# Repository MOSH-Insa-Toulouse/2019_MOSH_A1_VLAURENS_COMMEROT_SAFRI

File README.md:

<header>

 </header>
 <h1 style="text-align:center" >2019_MOSH_A1_VLAURENS_COMMEROT_SAFRI</h1>
<a href="./README_EN.md">Version Anglaise du README</a>

 ## Contenu

Ce projet KiCad contient le code source des TP sur Arduino et les fichiers de conception du shield réalisé dans le cadre du projet sur le capteur de Gaz", à savoir :
    La partie schématique, décrivant le circuit électronique implémenté (composants, routage des pins)
    La partie en couche, décrivant la forme de la carte, l’emplacement des différents éléments sur celle-ci et la trajectoire des pistes de routage.
    Une vu 3D montrant les résultat visuel de la carte lors qu'elle sera designé.

## 1. Travaux Pratiques sur Arduino

Ces travaux pratiques avaient pour principal objectif de nous apprendre à développer la partie intelligente de nos capteurs de gaz. En d'autres mots nous avons dans cette partie appris la composition d'une carte Arduino. Nous avons appris à pousser et tester des programmes sur le micro-controleur ATMEGA128 qui le compose.
Nous avons aussi appris à interfacer des circuit électroniques d'acquistion de données (capteurs) ou encore des circuits de puissances comme commander un cerveau moteur. 
Enfin nous avons développé un programme communicant via bluetooth avec le téléphne et qui permettait via une application android de commander l'allumage de LED.
Cette application android possédait des commande via button classique ou un module de reconnaissance vocale qui commandait l'arduino par des mot-clefs.

<figure class="image">
  
  <figcaption>Figure 1 : Aperçu de l'application Android</figcaption>
</figure>

# 2. PCB conception 

Dans un second temps, nous avons réalisé un projet qui visait à développer un module LoRa permettant de récupérer les valeurs de Gaz ambiant et les stocker sur une plateforme cloud "The think Network"

Nous avons donc dû interfacer l'antenne lora et surtout le capteur de gaz avec l'arduino uno.

Pour cela nous avons implémenté un montage (https://noullet-gei.gitlab.io/iss_analog/) dont le rôle est de filtrer le bruit et ainsi extraire toute l'information utile du capteur sans perturbation. Ci-dessous, le schéma d'acquisition de la donnée collectée par le capteur de Gaz.

<figure class="image">
  
  <figcaption>Figure 1 : Schéma électrique d'acquisition de la donnée du capteur</figcaption>
</figure>

Nous avons ensuite à l'aide kicad conçu une carte pouvant se gréffer à la carte Arduino Uno qui comporte le capteur de gaz et l'antenne LORA.
Pour ce faire nous avons implémenté via

<figure class="image">

  <figcaption>Figure 2 : EESCHEMA representation</figcaption>
</figure>

Nous avons tout d'abord, débuté par réaliser le circuit électronique. Il nous a donc fallu créer les composant électrique dont le premier que nous avons créé est le capteur de gaz et ses connecteur, ensuite nous les connecter entre-eux suivant le schéma de la figure 1.
Nous avons ensuite à l'aide de label lié les entrées et sortie de notre montage avec les PINs du module LORA que nous avons conçu, et les PINs de l'Arduino.
Ensuite nous avons vérifié les règles de routage afin de vérifié s'il n'ya vait pas de contradictions électriques.

Une fois le schéma électrique réalisé et vérifié, nous avons créé une empreinte pour chaque composant, notament pour le capteur de Gaz, le module Lora et l'ampli Opérationel. 
Enfin nous avons pu les router, les connecter comme illustré sur la figure 3.

<figure class="image">
  
  <figcaption>Figure 3 : Description du routage</figcaption>
</figure>

Nous savons qu'il est préférable, afin que le PCB, soit fabriqué à l'INSA de rassembler les routage sur une seule couche, afin de limiter le nombre de couche à deux, la coouche avant et arrière. De plus il nous à fallu resoecter certaines contraintes de taille des pistes et des trous. 
Afin donc de limiter le nombre de pistes et de concentrer le routage sur la face arrière seulement, nous avons conçu un plan de masse afin de se servir du bati du sheild comme masse.( Vue figure 4)
<figure class="image">
  
  <figcaption>Figure 4 : Description du routage avec une vue sur le pla de masse</figcaption>
</figure>

Nous vous laissons observer quelque vue réelle 3D de la carte finale.
<figure class="image">
  
  <figcaption>Figure 5 : Vue arrière 3D</figcaption>
</figure>

<figure class="image">
  
  <figcaption>Figure 5 : Vue avant 3D </figcaption>
</figure>

Un aperçu du routage

<figure class="image">
  
  <figcaption>Figure 5 : Vue 3D de côté</figcaption>
</figure>

# Pistes d'amélioration

Une piste sérieuse à améliorer serait d'ajouter des entrée pour prévoir une source d'alimentation au capteur afin qu'il soit autonôme. Une autre piste serait de créer le composent AOP en vue 3D. Enfin corrigé quelque problèmes de "pad near to pad" qui sont du au contarainte de taille de pad mposé par l'INSA et font que pour les capacité les pads se chevauche. 

# Conclusion

Au cours de ces TP nous avons eu l'occassion de programmer sur un Arduino.
Nous avons également appris à concevoir une carte électronique de bout en bout.
Ce module nous a appris à créer un capteur et à lui ajouter une certaine "intelligence" afin qu'il soit autônome
et puisse communiquer avec d'autres entité d'un système.
Nous avons réutilisé ces connaissances dans notre projet intégrateur durant lequel nous avons développé un module de capteurs intelligent pour surveiller la consommation d'énergie d'une douche.

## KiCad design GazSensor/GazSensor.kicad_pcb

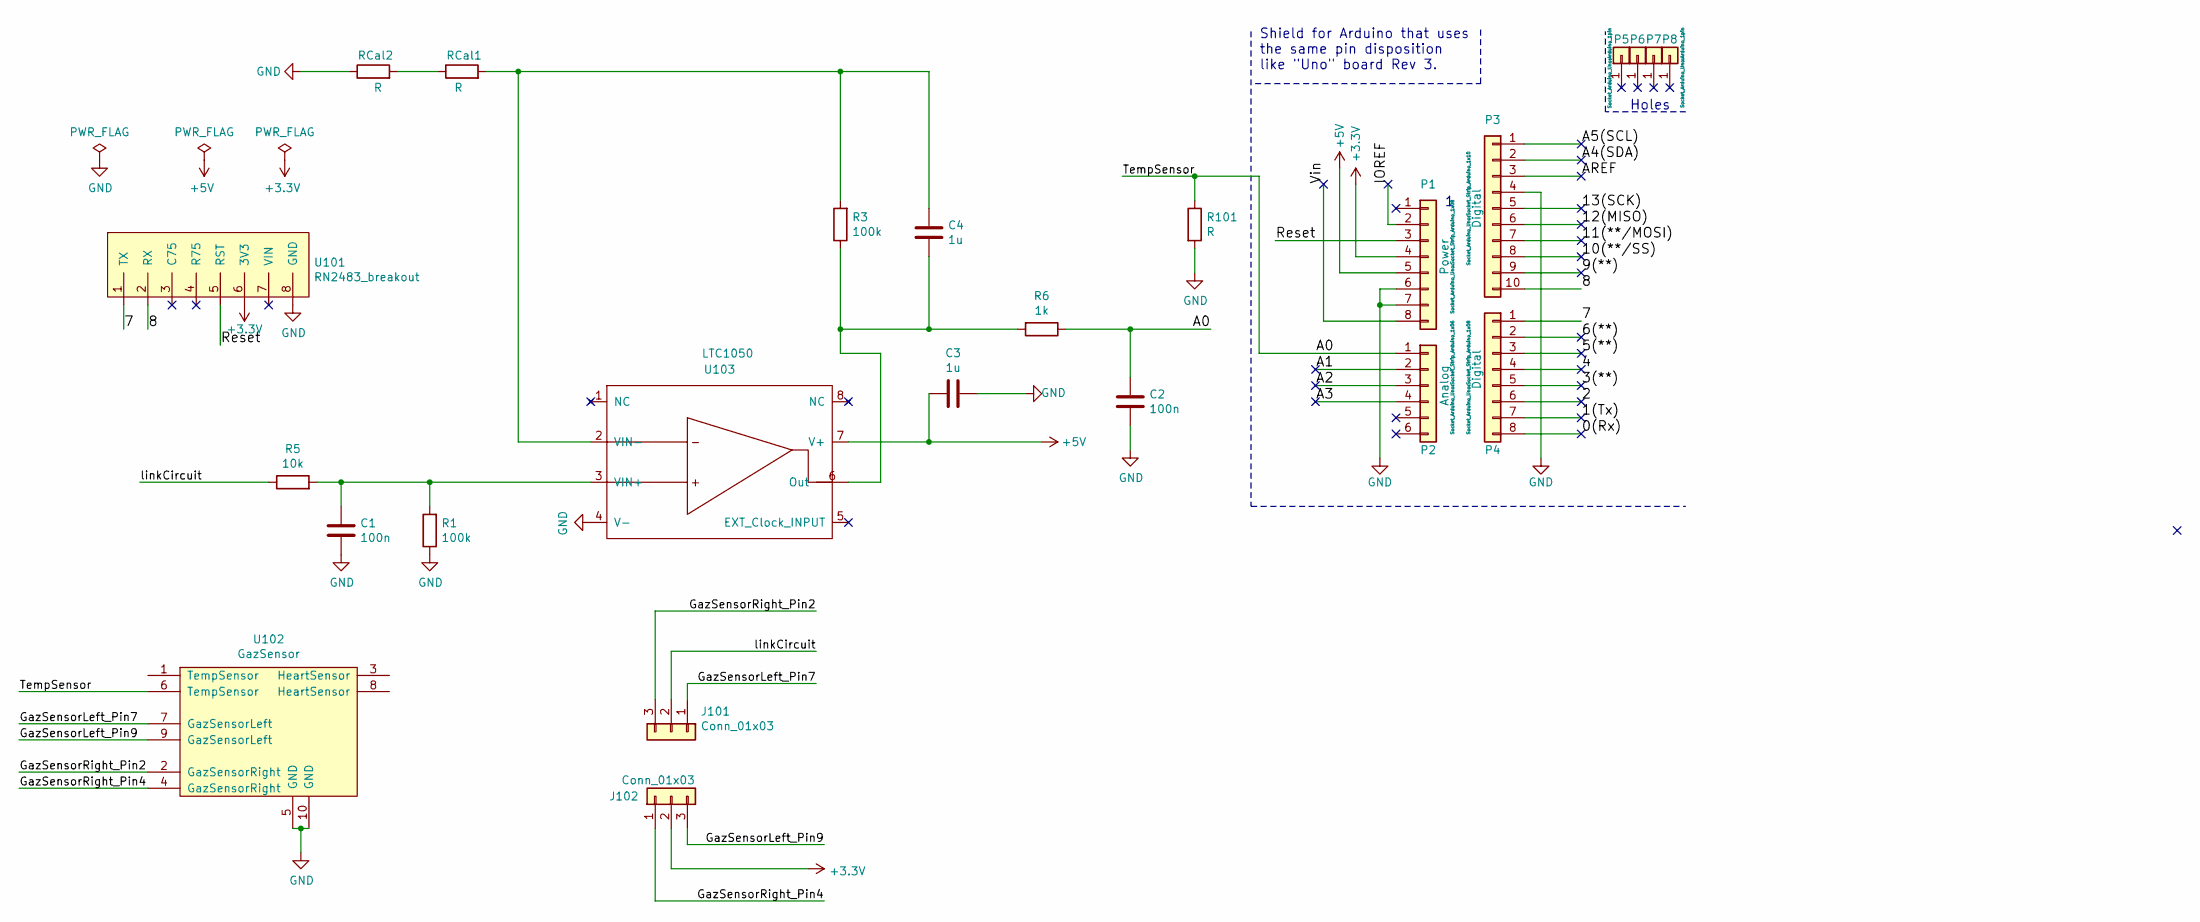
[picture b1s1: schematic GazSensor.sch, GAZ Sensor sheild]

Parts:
C1, C2: 100n; CP_Radial_D4.0mm_P1.50mm
C3, C4: 1u; CP_Radial_D4.0mm_P1.50mm
J101, J102: Conn_01x03; PinHeader_1x03_P2.00mm_Vertical
P1: Power; Socket_Strip_Arduino_1x08
P2: Analog; Socket_Strip_Arduino_1x06
P3: Digital; Socket_Strip_Arduino_1x10
P4: Digital; Socket_Strip_Arduino_1x08
P5, P6, P7, P8: CONN_01X01; Arduino_1pin
R1, R3: 100k; R_Axial_DIN0207_L6.3mm_D2.5mm_P7.62mm_Horizontal
R5: 10k; R_Axial_DIN0207_L6.3mm_D2.5mm_P7.62mm_Horizontal
R6: 1k; R_Axial_DIN0207_L6.3mm_D2.5mm_P7.62mm_Horizontal
R101: R; R_Axial_DIN0207_L6.3mm_D2.5mm_P7.62mm_Horizontal
RCal1, RCal2: R; R_Axial_DIN0207_L6.3mm_D2.5mm_P7.62mm_Horizontal
U101: RN2483_breakout; RN2483_Breakout
U102: GazSensor; TO-5-10_Window
U103: LTC1050; DIP-8_W7.62mm_LongPads

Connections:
+3V3: J102.2, P1.4, U101.6 (3V3)
+5V: C3.2, P1.5, U103.7 (V+)
/0(Rx): P4.8
/1(Tx): P4.7
/2: P4.6
/3(**): P4.5
/4: P4.4
/5(**): P4.3
/6(**): P4.2
/7: P4.1, U101.1 (TX)
/8: P3.10, U101.2 (RX)
/9(**): P3.9
/10(**/SS): P3.8
/11(**/MOSI): P3.7
/12(MISO): P3.6
/13(SCK): P3.5
/A0: C2.1, P2.1, R6.1, R101.1, U102.6 (TempSensor)
/A1: P2.2
/A2: P2.3
/A3: P2.4
/A4(SDA): P3.2
/A5(SCL): P3.1
/AREF: P3.3
/GazSensorLeft_Pin7: J101.1, U102.7 (GazSensorLeft)
/GazSensorLeft_Pin9: J102.3, U102.9 (GazSensorLeft)
/GazSensorRight_Pin2: J101.3, U102.2 (GazSensorRight)
/GazSensorRight_Pin4: J102.1, U102.4 (GazSensorRight)
/IOREF: P1.2
/Reset: P1.3, U101.5 (RST)
/Vin: P1.8
/linkCircuit: J101.2, R5.1
GND: C1.2, C2.2, C3.1, P1.6, P1.7, P3.4, R1.1, R101.2, RCal2.1, U101.8 (GND), U102.5 (GND), U102.10 (GND), U103.4 (V-)
unnamed: C1.1, R1.2, R5.2, U103.3 (VIN+)
unnamed: C4.1, R3.2, RCal1.2, U103.2 (VIN-)
unnamed: C4.2, R3.1, R6.2, U103.6 (Out)
unnamed: RCal1.1, RCal2.2

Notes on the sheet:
Holes
Shield for Arduino that uses the same pin disposition like "Uno" board Rev 3.

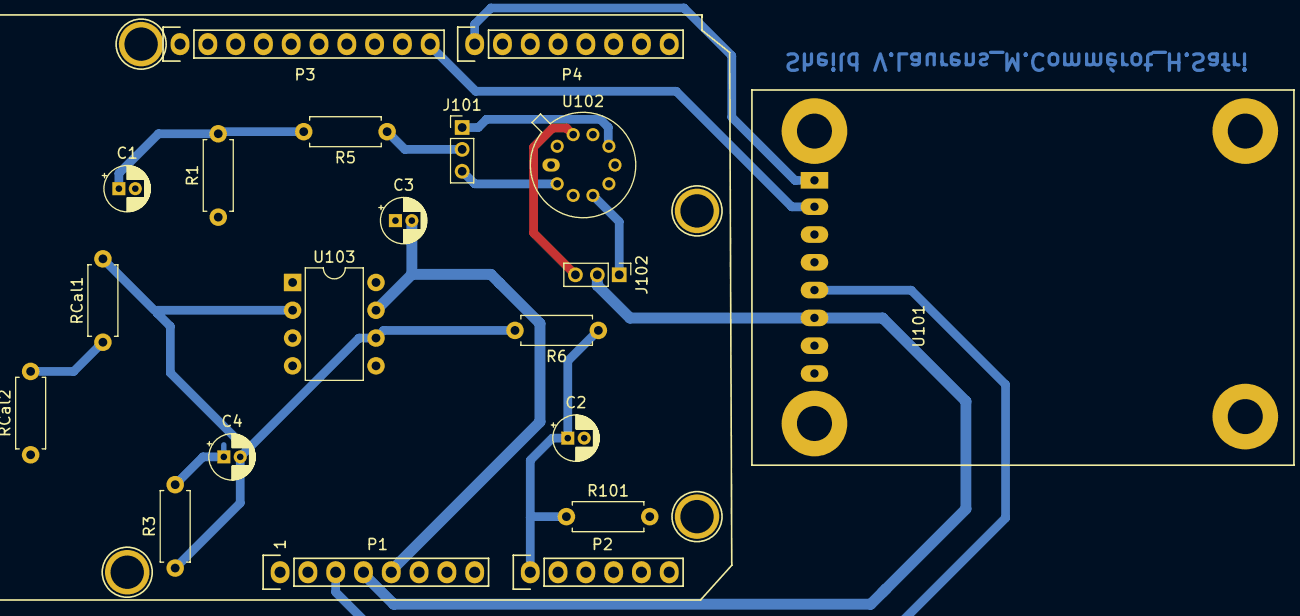
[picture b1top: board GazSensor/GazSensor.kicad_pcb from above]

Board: 2 copper layers, 24 parts (0 on the bottom side), 16 nets.

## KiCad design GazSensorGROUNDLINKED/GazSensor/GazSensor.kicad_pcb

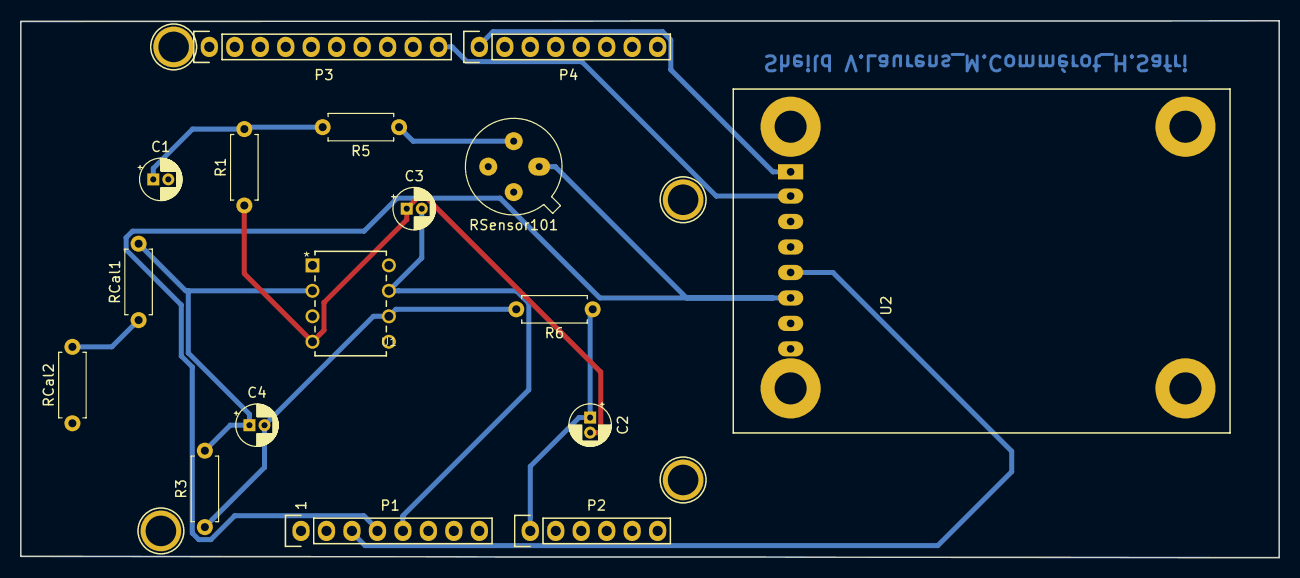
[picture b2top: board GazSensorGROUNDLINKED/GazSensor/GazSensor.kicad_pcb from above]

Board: 2 copper layers, 125.5 x 53.5 mm, 21 parts (0 on the bottom side), 12 nets.

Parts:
C1, C2: 100n; CP_Radial_D4.0mm_P1.50mm
C3, C4: 1u; CP_Radial_D4.0mm_P1.50mm
P1: Power; Socket_Strip_Arduino_1x08
P2: Analog; Socket_Strip_Arduino_1x06
P3: Digital; Socket_Strip_Arduino_1x10
P4: Digital; Socket_Strip_Arduino_1x08
P5, P6, P7, P8: CONN_01X01; Arduino_1pin
R1, R3: 100k; R_Axial_DIN0207_L6.3mm_D2.5mm_P7.62mm_Horizontal
R5: 10k; R_Axial_DIN0207_L6.3mm_D2.5mm_P7.62mm_Horizontal
R6: 1k; R_Axial_DIN0207_L6.3mm_D2.5mm_P7.62mm_Horizontal
RCal1, RCal2: R; R_Axial_DIN0207_L6.3mm_D2.5mm_P7.62mm_Horizontal
RSensor101: R; GazSensor
U1: LTC1050; PDIP-8_N
U2: RN2483_breakout; RN2483_Breakout

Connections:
+3V3: P1.4, RSensor101.1, U2.6
+5V: C3.2, P1.5, U1.7
/7: P4.1, U2.1
/8: P3.10, U2.2
/A0: C2.1, P2.1, R6.1
/Reset: P1.3, U2.5
GND: C1.2, C2.2, C3.1, P1.6, P1.7, P3.4, R1.1, RCal2.1, U1.4, U2.8
unnamed: C1.1, R1.2, R5.2, U1.3
unnamed: C4.1, R3.2, RCal1.2, U1.2
unnamed: C4.2, R3.1, R6.2, U1.6
unnamed: R5.1, RSensor101.2
unnamed: RCal1.1, RCal2.2

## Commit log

2019-12-21 Electrical rules ok
    But PCB still to do
2019-12-22 Sheild PCB
2019-12-28 New sheild
2019-12-28 New PCB with track linking ground
2019-12-28 images
2020-01-04 README
2020-01-11 Rules respected
2020-01-11 PCB Good
2020-01-12 Update README.md
    Conclusion
2020-01-18 Last Version with Aime Gaz Sensor
2020-01-18 Image of last sheild
2020-01-19 Last Commit
2020-01-21 Last kicad version
2020-01-21 Add pdf for manufacturing
